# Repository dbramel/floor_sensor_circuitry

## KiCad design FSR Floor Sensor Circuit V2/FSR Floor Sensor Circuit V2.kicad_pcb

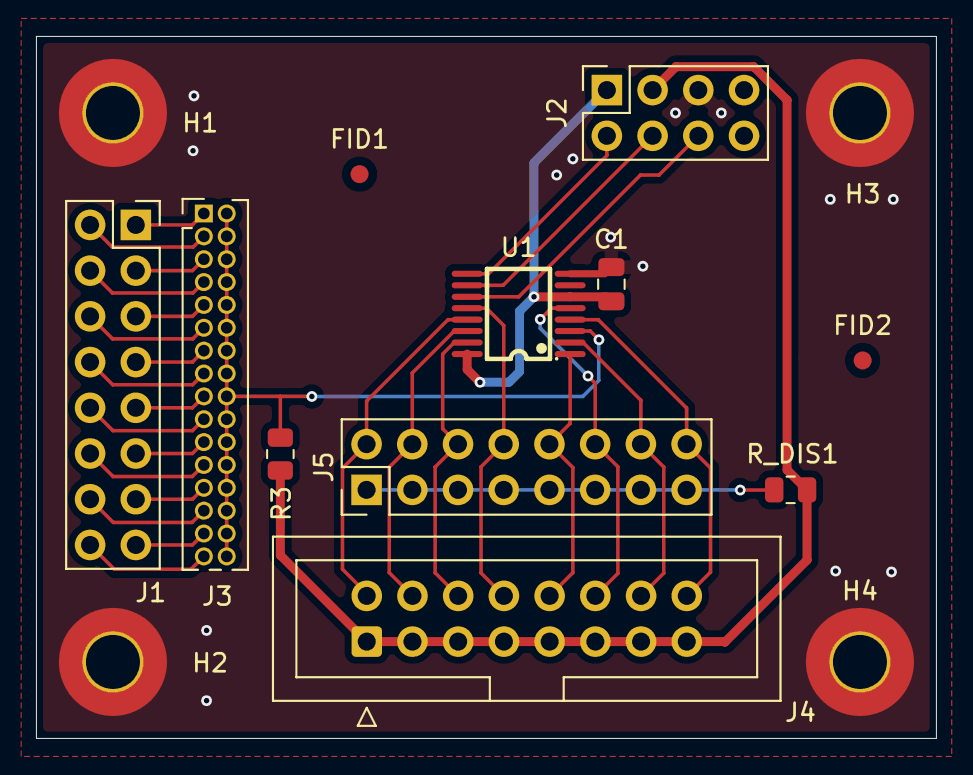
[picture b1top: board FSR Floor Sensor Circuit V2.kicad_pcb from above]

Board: 2 copper layers, 50.0 x 39.0 mm, 15 parts (0 on the bottom side), 32 nets.

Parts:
C1: 0.1uF; C_0805_2012Metric
FID1, FID2: Fiducial; Fiducial_1mm_Mask2mm
H1, H2, H3, H4: MountingHole_Pad; MountingHole_3mm_Pad_TopBottom
J1: Daughterboard Connector; PinSocket_2x08_P2.54mm_Vertical
J2: MCU Connector; PinSocket_2x04_P2.54mm_Vertical
J3: Board Select Jumper; PinHeader_2x16_P1.27mm_Vertical
J4: FSR Ribbon Cable; IDC-Header_2x08_P2.54mm_Vertical
J5: FSR Disable Jumper; PinHeader_2x08_P2.54mm_Vertical
R3: 10M; R_0805_2012Metric
R_DIS1: 1k; R_0805_2012Metric
U1: TMUX1308APWR; TSSOP-16_L5.0-W4.4-P0.64-LS6.4-BL

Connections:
+5V: C1.1, J2.1, U1.6 (~EN), U1.16 (VDD)
/2V5_REF: J2.3, J4.1, J4.3, J4.5, J4.7, J4.9, J4.11, J4.13, J4.15, R3.2, R_DIS1.1
/Daughter_1: J1.1, J3.1
/Daughter_2: J1.2, J3.3
/Daughter_3: J1.3, J3.5
/Daughter_4: J1.4, J3.7
/Daughter_5: J1.5, J3.9
/Daughter_6: J1.6, J3.11
/Daughter_7: J1.7, J3.13
/Daughter_8: J1.8, J3.15
/Daughter_9: J1.9, J3.17
/Daughter_10: J1.10, J3.19
/Daughter_11: J1.11, J3.21
/Daughter_12: J1.12, J3.23
/Daughter_13: J1.13, J3.25
/Daughter_14: J1.14, J3.27
/Daughter_15: J1.15, J3.29
/Daughter_16: J1.16, J3.31
/FSR Daughterboard/FSR_1: J4.2, J5.2, U1.13 (S0)
/FSR Daughterboard/FSR_2: J4.4, J5.4, U1.14 (S1)
/FSR Daughterboard/FSR_3: J4.6, J5.6, U1.15 (S2)
/FSR Daughterboard/FSR_4: J4.8, J5.8, U1.12 (S3)
/FSR Daughterboard/FSR_5: J4.10, J5.10, U1.1 (S4)
/FSR Daughterboard/FSR_6: J4.12, J5.12, U1.5 (S5)
/FSR Daughterboard/FSR_7: J4.14, J5.14, U1.2 (S6)
/FSR Daughterboard/FSR_8: J4.16, J5.16, U1.4 (S7)
/FSR Daughterboard/FSR_DIS: J5.1, J5.3, J5.5, J5.7, J5.9, J5.11, J5.13, J5.15, R_DIS1.2
/FSR Daughterboard/Selected_FSR: J3.2, J3.4, J3.6, J3.8, J3.10, J3.12, J3.14, J3.16, J3.18, J3.20, J3.22, J3.24, J3.26, J3.28, J3.30, J3.32, R3.1, U1.3 (D)
/FSR_Mux_0: J2.6, U1.11 (A0)
/FSR_Mux_1: J2.4, U1.10 (A1)
/FSR_Mux_2: J2.2, U1.9 (A2)
GND: C1.2, H1.1 (1_1), H2.1 (1_1), H3.1 (1_1), H4.1 (1_1), J2.5, U1.8 (GND)

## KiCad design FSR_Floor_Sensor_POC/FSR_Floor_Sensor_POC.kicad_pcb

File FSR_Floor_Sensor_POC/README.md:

# FSR Floor Sensor Measurement POC

The schematic uses the installed KiCad library symbols for the passive parts and connectors: `Device:R`, `Device:C`, `Connector_Generic:Conn_02x08_Odd_Even` (J2), and `Connector_Generic:Conn_02x10_Odd_Even` (J1). Custom local symbols remain for ADS1256, ADG708, and REF5025.

J2 is the 2x8 FSR ribbon connector. Odd pins 1, 3, 5, 7, 9, 11, 13, and 15 share `VEXC_2V5`; even pins 2, 4, 6, 8, 10, 12, 14, and 16 carry `FSR0_NODE` through `FSR7_NODE`. Each sensor return connects to the corresponding ADS1256 AIN0–AIN7 input and U2 S1–S8.

U2 selects one sensor to `LOAD_NODE`. U3 selects a load resistor from 1 kΩ through 1 MΩ between `LOAD_NODE` and AGND. The mux address and enable signals are shared. U4 provides the 2.5 V reference for sensor excitation and ADS1256 VREFP; VREFN and AINCOM connect to AGND.

J1 is a generic 2x10 host connection for mux control, SPI, ADC control/clock/GPIO, +5VA, +3V3, and AGND. Assign footprints to match the actual build before PCB layout. See `BOM.csv` for the component summary.

Validation: KiCad CLI exported the schematic netlist successfully and ERC reported 0 errors and 0 warnings.

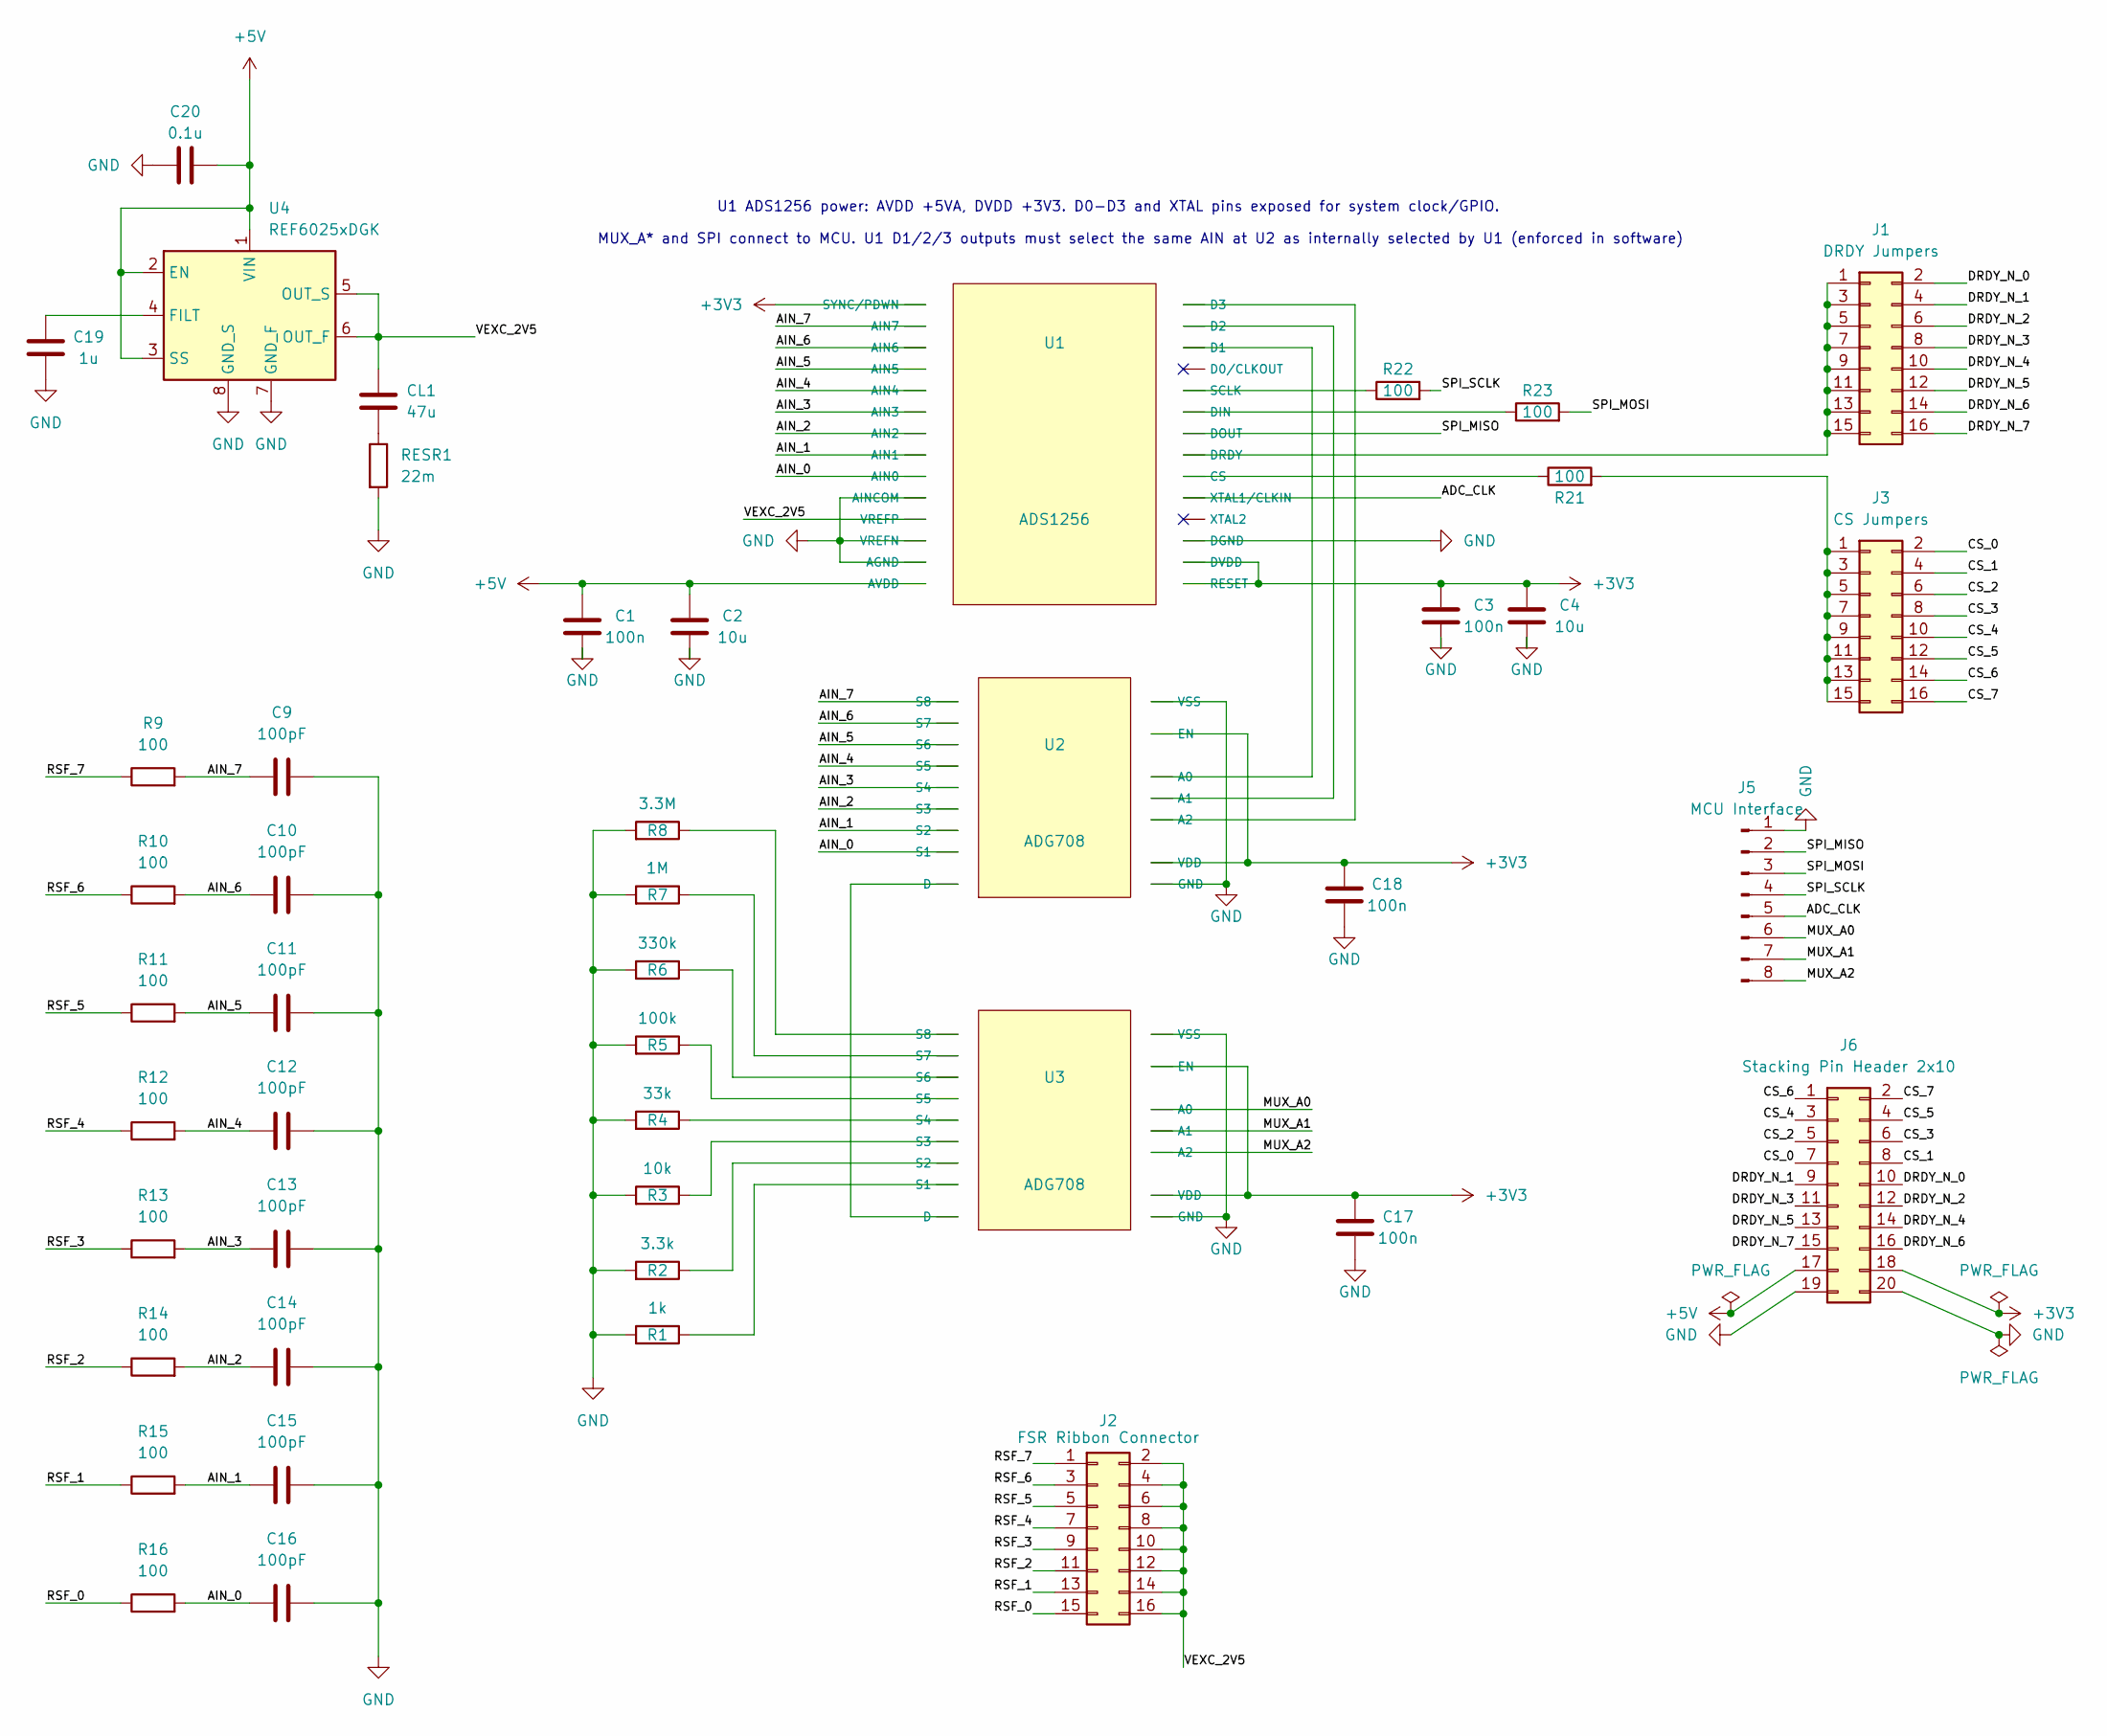
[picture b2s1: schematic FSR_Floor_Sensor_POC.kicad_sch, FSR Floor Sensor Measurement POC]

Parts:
C1, C3, C17, C18: 100n; C_0805_2012Metric
C2, C4: 10u; C_0805_2012Metric
C9, C10, C11, C12, C13, C14, C15, C16: 100pF; C_0805_2012Metric
C19: 1u; C_0805_2012Metric
C20: 0.1u; C_0805_2012Metric
CL1: 47u; C_0805_2012Metric
J1: DRDY Jumpers; PinHeader_2x08_P1.27mm_Vertical
J2: FSR Ribbon Connector; IDC-Header_2x08_P2.54mm_Vertical
J3: CS Jumpers; PinHeader_2x08_P1.27mm_Vertical
J5: MCU Interface; PinHeader_1x08_P2.54mm_Vertical
J6: Stacking Pin Header 2x10; PinHeader_2x10_P2.54mm_Vertical
R1: 1k; R_0805_2012Metric
R2: 3.3k; R_0805_2012Metric
R3: 10k; R_0805_2012Metric
R4: 33k; R_0805_2012Metric
R5: 100k; R_0805_2012Metric
R6: 330k; R_0805_2012Metric
R7: 1M; R_0805_2012Metric
R8: 3.3M; R_0805_2012Metric
R9, R10, R11, R12, R13, R14, R15, R16, R21, R22, R23: 100; R_0805_2012Metric
RESR1: 22m; R_0805_2012Metric
U1: ADS1256; SSOP-28_5.3x10.2mm_P0.65mm
U2, U3: ADG708; TSSOP-16_4.4x5mm_P0.65mm
U4: REF6025xDGK; VSSOP-8_3x3mm_P0.65mm

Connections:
+3V3: C3.1, C4.1, C17.1, C18.1, J6.18, U1.14 (SYNC/PDWN), U1.15 (RESET), U1.16 (DVDD), U2.2 (EN), U2.13 (VDD), U3.2 (EN), U3.13 (VDD)
+5V: C1.1, C2.1, C20.2, J6.17, U1.1 (AVDD), U4.1 (VIN), U4.2 (EN), U4.3 (SS)
/ADC_CLK: J5.5, U1.19 (XTAL1/CLKIN)
/AIN_0: C16.1, R16.2, U1.6 (AIN0), U2.4 (S1)
/AIN_1: C15.1, R15.2, U1.7 (AIN1), U2.5 (S2)
/AIN_2: C14.1, R14.2, U1.8 (AIN2), U2.6 (S3)
/AIN_3: C13.1, R13.2, U1.9 (AIN3), U2.7 (S4)
/AIN_4: C12.1, R12.2, U1.10 (AIN4), U2.12 (S5)
/AIN_5: C11.1, R11.2, U1.11 (AIN5), U2.11 (S6)
/AIN_6: C10.1, R10.2, U1.12 (AIN6), U2.10 (S7)
/AIN_7: C9.1, R9.2, U1.13 (AIN7), U2.9 (S8)
/CS_0: J3.2, J6.7
/CS_1: J3.4, J6.8
/CS_2: J3.6, J6.5
/CS_3: J3.8, J6.6
/CS_4: J3.10, J6.3
/CS_5: J3.12, J6.4
/CS_6: J3.14, J6.1
/CS_7: J3.16, J6.2
/DRDY_N_0: J1.2, J6.10
/DRDY_N_1: J1.4, J6.9
/DRDY_N_2: J1.6, J6.12
/DRDY_N_3: J1.8, J6.11
/DRDY_N_4: J1.10, J6.14
/DRDY_N_5: J1.12, J6.13
/DRDY_N_6: J1.14, J6.16
/DRDY_N_7: J1.16, J6.15
/MUX_A0: J5.6, U3.1 (A0)
/MUX_A1: J5.7, U3.16 (A1)
/MUX_A2: J5.8, U3.15 (A2)
/RSF_0: J2.15, R16.1
/RSF_1: J2.13, R15.1
/RSF_2: J2.11, R14.1
/RSF_3: J2.9, R13.1
/RSF_4: J2.7, R12.1
/RSF_5: J2.5, R11.1
/RSF_6: J2.3, R10.1
/RSF_7: J2.1, R9.1
/SPI_MISO: J5.2, U1.22 (DOUT)
/SPI_MOSI: J5.3, R23.2
/SPI_SCLK: J5.4, R22.2
/VEXC_2V5: CL1.1, J2.2, J2.4, J2.6, J2.8, J2.10, J2.12, J2.14, J2.16, U1.4 (VREFP), U4.5 (OUT_S), U4.6 (OUT_F)
GND: C1.2, C2.2, C3.2, C4.2, C9.2, C10.2, C11.2, C12.2, C13.2, C14.2, C15.2, C16.2, C17.2, C18.2, C19.2, C20.1, J5.1, J6.19, J6.20, R1.2, R2.2, R3.2, R4.2, R5.2, R6.2, R7.2, R8.2, RESR1.2, U1.2 (AGND), U1.3 (VREFN), U1.5 (AINCOM), U1.17 (DGND), U2.3 (VSS), U2.14 (GND), U3.3 (VSS), U3.14 (GND), U4.7 (GND_F), U4.8 (GND_S)
unnamed: CL1.2, RESR1.1
unnamed: J1.1, J1.3, J1.5, J1.7, J1.9, J1.11, J1.13, J1.15, U1.21 (DRDY)
unnamed: J3.1, J3.3, J3.5, J3.7, J3.9, J3.11, J3.13, J3.15, R21.2
unnamed: R21.1, U1.20 (CS)
unnamed: U1.26 (D1), U2.1 (A0)
unnamed: U1.27 (D2), U2.16 (A1)
unnamed: U1.28 (D3), U2.15 (A2)
unnamed: R23.1, U1.23 (DIN)
unnamed: R22.1, U1.24 (SCLK)
unnamed: U2.8 (D), U3.8 (D)
unnamed: R1.1, U3.4 (S1)
unnamed: R2.1, U3.5 (S2)
unnamed: R3.1, U3.6 (S3)
unnamed: R4.1, U3.7 (S4)
unnamed: R5.1, U3.12 (S5)
unnamed: R6.1, U3.11 (S6)
unnamed: R7.1, U3.10 (S7)
unnamed: R8.1, U3.9 (S8)
unnamed: C19.1, U4.4 (FILT)

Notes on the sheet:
U1 ADS1256 power: AVDD +5VA, DVDD +3V3. D0-D3 and XTAL pins exposed for system clock/GPIO.
MUX_A* and SPI connect to MCU. U1 D1/2/3 outputs must select the same AIN at U2 as internally selected by U1 (enforced in software)

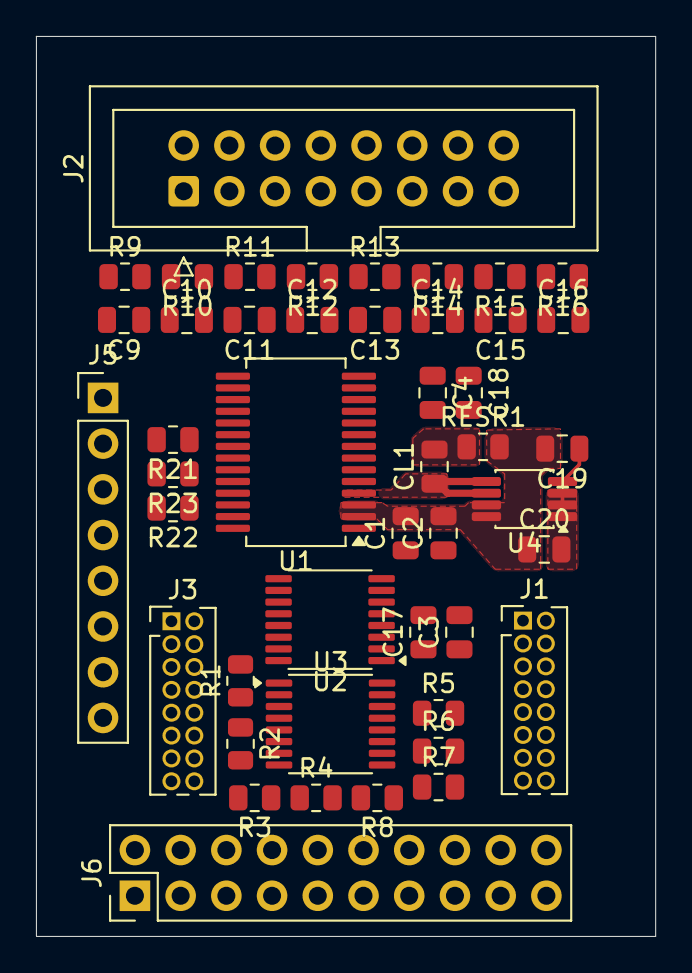
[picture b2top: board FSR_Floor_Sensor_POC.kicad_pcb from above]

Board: 2 copper layers, 34.4 x 50.0 mm, 46 parts (0 on the bottom side), 62 nets.

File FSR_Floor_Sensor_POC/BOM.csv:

"Reference","Value","Datasheet","Footprint","Qty","DNP","Description"
"C1,C3,C17,C18","100n","","Capacitor_SMD:C_0805_2012Metric","4","","X7R or X5R ceramic"
"C2,C4","10u","","Capacitor_SMD:C_0805_2012Metric","2","","X7R"
"C9,C10,C11,C12,C13,C14,C15,C16","100pF","","Capacitor_SMD:C_0805_2012Metric","8","","Unpolarized capacitor COG/NPO Ceramic"
"C19","1u","","Capacitor_SMD:C_0805_2012Metric","1","","X7R or X5R ceramic"
"C20","0.1u","","Capacitor_SMD:C_0805_2012Metric","1","","X7R or X5R ceramic"
"CL1","47u","","Capacitor_SMD:C_0805_2012Metric","1","","X7R deramic"
"J1","DRDY Jumpers","","Connector_PinHeader_2.54mm:PinHeader_2x08_P2.54mm_Vertical","1","","Generic connector, double row, 02x08, odd/even pin numbering scheme (row 1 odd numbers, row 2 even numbers), script generated (kicad-library-utils/schlib/autogen/connector/)"
"J2","FSR Ribbon Connector","","Connector_IDC:IDC-Header_2x08_P2.54mm_Vertical","1","",""
"J3","CS Jumpers","","Connector_PinHeader_2.54mm:PinHeader_2x08_P2.54mm_Vertical","1","","Generic connector, double row, 02x08, odd/even pin numbering scheme (row 1 odd numbers, row 2 even numbers), script generated (kicad-library-utils/schlib/autogen/connector/)"
"J4","Stackable Header","https://cdn-shop.adafruit.com/product-files/2223/P2223+F201-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","Connector_PinSocket_2.54mm:PinSocket_2x16_P2.54mm_Vertical","1","","2×16, 2.54 mm pitch, through-hole stacking header; female sockets on top, extra-long square male tails through the PCB on the bottom; straight/vertical; board-to-board stackable. Specify pin length and stack height to match the mating boards."
"R1","1k","","Resistor_SMD:R_0805_2012Metric","1","",""
"R2","3.3k","","Resistor_SMD:R_0805_2012Metric","1","",""
"R3","10k","","Resistor_SMD:R_0805_2012Metric","1","",""
"R4","33k","","Resistor_SMD:R_0805_2012Metric","1","",""
"R5","100k","","Resistor_SMD:R_0805_2012Metric","1","",""
"R6","330k","","Resistor_SMD:R_0805_2012Metric","1","",""
"R7","1M","","Resistor_SMD:R_0805_2012Metric","1","",""
"R8","3.3M","","Resistor_SMD:R_0805_2012Metric","1","",""
"R9,R10,R11,R12,R13,R14,R15,R16,R21,R22,R23","100","","Resistor_SMD:R_0805_2012Metric","11","","Resistor"
"RESR1","22m","","Resistor_SMD:R_0805_2012Metric","1","","Resistor"
"U1","ADS1256","https://www.ti.com/lit/ds/symlink/ads1255.pdf?ts=1790116895214","Package_SO:SSOP-28_5.3x10.2mm_P0.65mm","1","",""
"U2,U3","ADG708","https://www.analog.com/media/en/technical-documentation/data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","Package_SO:TSSOP-16_4.4x5mm_P0.65mm","2","",""
"U4","REF6025xDGK","https://www.ti.com/lit/ds/symlink/ref6025.pdf","Package_SO:VSSOP-8_3x3mm_P0.65mm","1","","2.5V 0.05% 4mA Extremely Low Noise High Precision Voltage Reference, VSSOP-8"
